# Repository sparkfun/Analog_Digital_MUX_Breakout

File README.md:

Analog/Digital MUX Breakout
===========================

[  
*Analog/Digital MUX Breakout (BOB-09056)*](https://www.sparkfun.com/products/9056)

This a breakout board for the 16-channel Analog/Digital Multiplexer/Demultiplier CD74HC4067. 

Repository Contents
-------------------
* **/Hardware** - All Eagle design files (.brd, .sch)

License Information
-------------------
The hardware is released under [Creative Commons Share-alike 3.0](http://creativecommons.org/licenses/by-sa/3.0/).

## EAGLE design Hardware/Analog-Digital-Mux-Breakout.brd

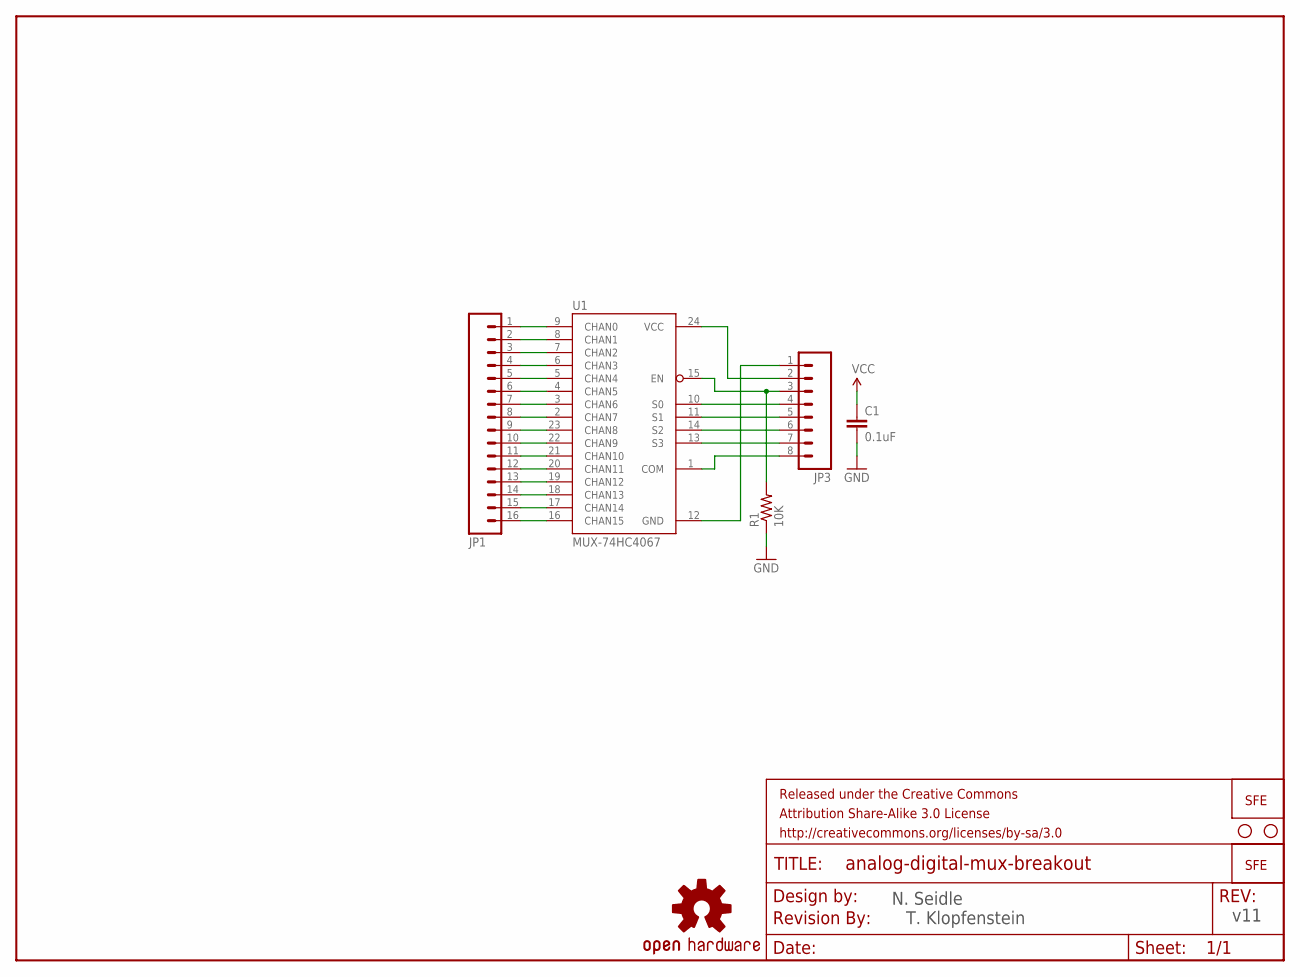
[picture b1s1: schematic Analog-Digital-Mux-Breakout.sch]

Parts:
C1: 0.1uF; 0603
FRAME1: FRAME-LETTER; CREATIVE_COMMONS
JP1: M16PTH; 1X16
JP3: M081X08; 1X08
LOGO1: OSHW-LOGOL; OSHW-LOGO-L
LOGO2: LOGO-SFESK; SFE-LOGO-FLAME
R1: 10K; 0603
STANDOFF1, STANDOFF2: STAND-OFF
U1: MUX-74HC4067; SSOP24
U$1: LOGO-SFENEW; SFE-NEW-WEBLOGO
U$2: REVISION

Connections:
C0: JP1.1, U1.9 (CHAN0)
C1: JP1.2, U1.8 (CHAN1)
C2: JP1.3, U1.7 (CHAN2)
C3: JP1.4, U1.6 (CHAN3)
C4: JP1.5, U1.5 (CHAN4)
C5: JP1.6, U1.4 (CHAN5)
C6: JP1.7, U1.3 (CHAN6)
C7: JP1.8, U1.2 (CHAN7)
C8: JP1.9, U1.23 (CHAN8)
C9: JP1.10, U1.22 (CHAN9)
C10: JP1.11, U1.21 (CHAN10)
C11: JP1.12, U1.20 (CHAN11)
C12: JP1.13, U1.19 (CHAN12)
C13: JP1.14, U1.18 (CHAN13)
C14: JP1.15, U1.17 (CHAN14)
C15: JP1.16, U1.16 (CHAN15)
EN: JP3.3, R1.2, U1.15 (EN)
GND: C1.2, JP3.1, R1.1, U1.12 (GND)
S0: JP3.4, U1.10 (S0)
S1: JP3.5, U1.11 (S1)
S2: JP3.6, U1.14 (S2)
S3: JP3.7, U1.13 (S3)
SIG: JP3.8, U1.1 (COM)
VCC: C1.1, JP3.2, U1.24 (VCC)

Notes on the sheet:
v11
N. Seidle
T. Klopfenstein

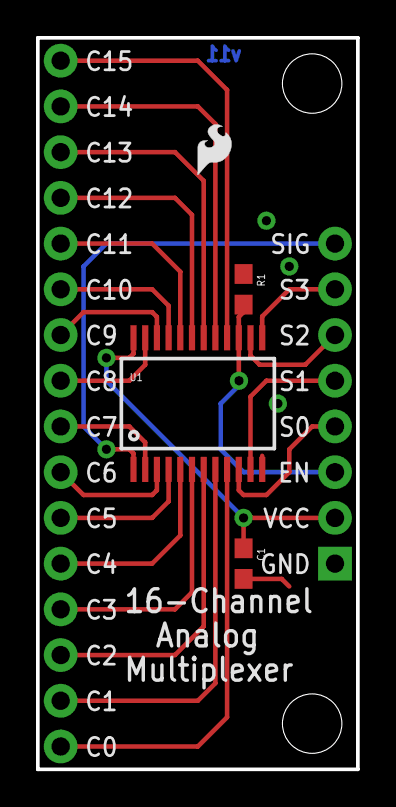
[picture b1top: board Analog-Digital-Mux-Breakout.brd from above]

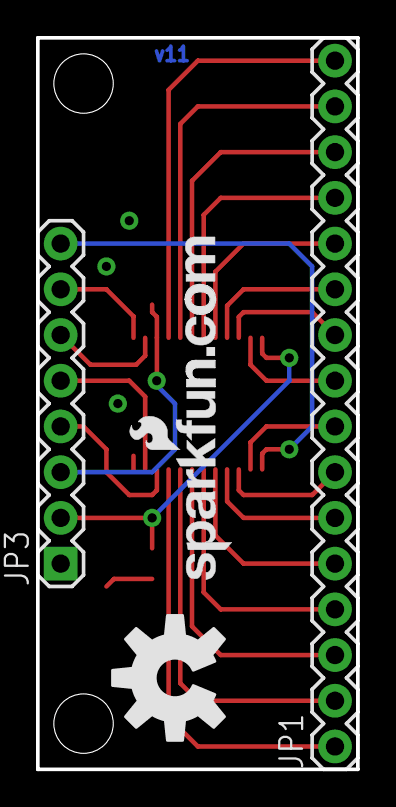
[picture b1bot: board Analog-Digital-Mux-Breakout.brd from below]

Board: 2 copper layers, 17.8 x 40.6 mm, 12 parts (4 on the bottom side), 24 nets.

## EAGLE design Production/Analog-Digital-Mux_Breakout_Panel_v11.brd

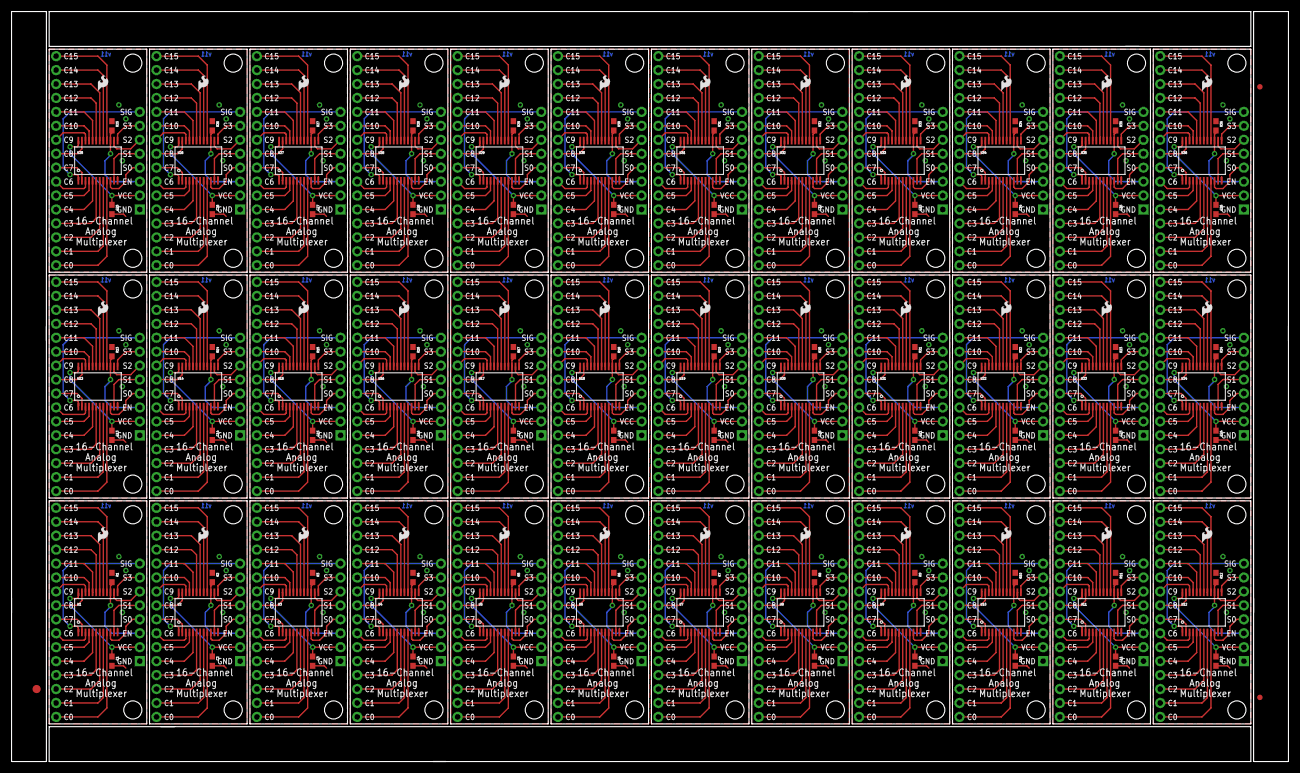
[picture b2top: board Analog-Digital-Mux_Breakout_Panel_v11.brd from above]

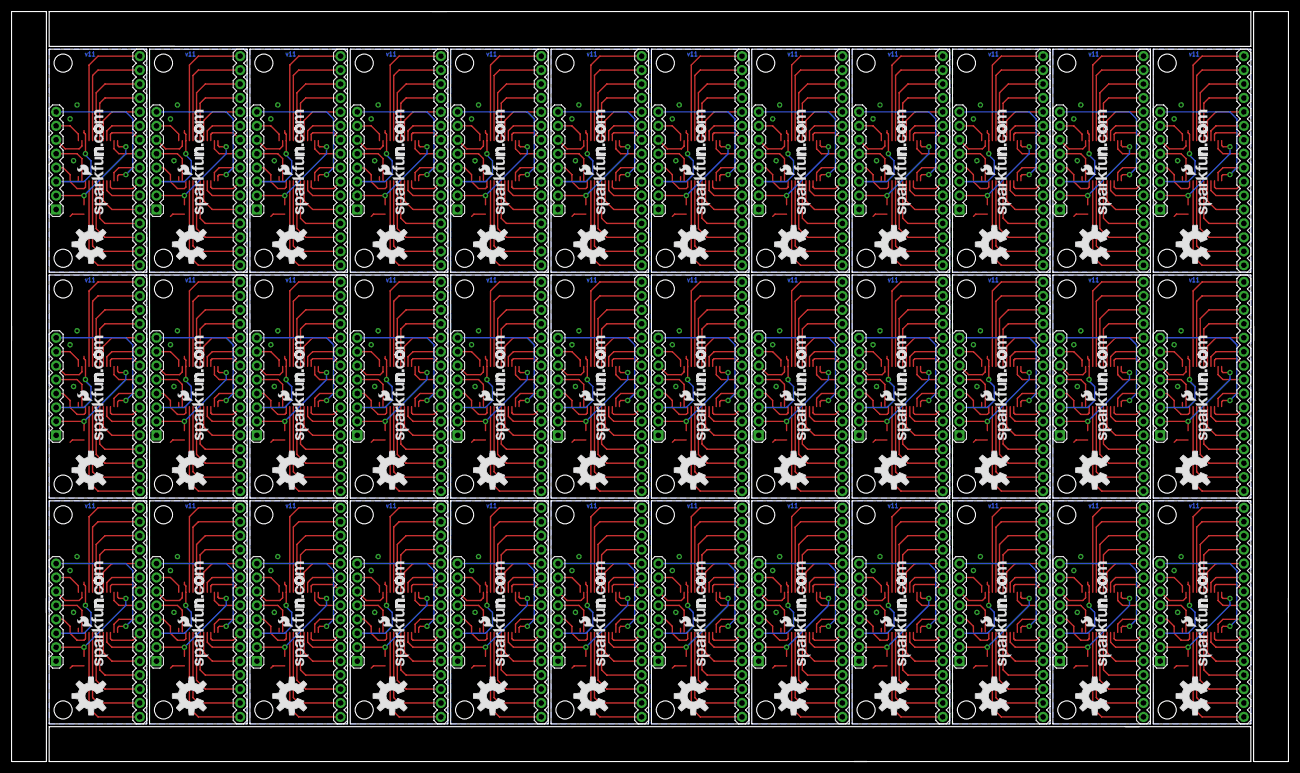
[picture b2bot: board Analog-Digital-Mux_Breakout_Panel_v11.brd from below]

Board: 2 copper layers, 232.7 x 136.7 mm, 363 parts (144 on the bottom side), 864 nets.

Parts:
C1, C2, C3, C4, C5, C6, C7, C8, C9, C10, C11, C12, C13, C14, C15, C16, C17, C18, C19, C20, C21, C22, C23, C24, C25, C26, C27, C28, C29, C30, C31, C32, C33, C34, C35, C36: 0.1uF; 0603
E$1: FIDUCIAL-1.5X3
E$5, E$6: FIDUCIAL-1X2
JP1, JP2, JP5, JP7, JP9, JP11, JP13, JP15, JP17, JP19, JP21, JP23, JP25, JP27, JP29, JP31, JP33, JP35, JP37, JP39, JP41, JP43, JP45, JP47, JP49, JP51, JP53, JP55, JP57, JP59, JP61, JP63, JP65, JP67, JP69, JP71: 1X16
JP3, JP4, JP6, JP8, JP10, JP12, JP14, JP16, JP18, JP20, JP22, JP24, JP26, JP28, JP30, JP32, JP34, JP36, JP38, JP40, JP42, JP44, JP46, JP48, JP50, JP52, JP54, JP56, JP58, JP60, JP62, JP64, JP66, JP68, JP70, JP72: 1X08
LOGO1, LOGO3, LOGO5, LOGO7, LOGO9, LOGO11, LOGO13, LOGO15, LOGO17, LOGO19, LOGO21, LOGO23, LOGO25, LOGO27, LOGO29, LOGO31, LOGO33, LOGO35, LOGO37, LOGO39, LOGO41, LOGO43, LOGO45, LOGO47, LOGO49, LOGO51, LOGO53, LOGO55, LOGO57, LOGO59, LOGO61, LOGO63, LOGO65, LOGO67, LOGO69, LOGO71: OSHW-LOGOL; OSHW-LOGO-L
LOGO2, LOGO4, LOGO6, LOGO8, LOGO10, LOGO12, LOGO14, LOGO16, LOGO18, LOGO20, LOGO22, LOGO24, LOGO26, LOGO28, LOGO30, LOGO32, LOGO34, LOGO36, LOGO38, LOGO40, LOGO42, LOGO44, LOGO46, LOGO48, LOGO50, LOGO52, LOGO54, LOGO56, LOGO58, LOGO60, LOGO62, LOGO64, LOGO66, LOGO68, LOGO70, LOGO72: LOGO-SFESK; SFE-LOGO-FLAME
R1, R2, R3, R4, R5, R6, R7, R8, R9, R10, R11, R12, R13, R14, R15, R16, R17, R18, R19, R20, R21, R22, R23, R24, R25, R26, R27, R28, R29, R30, R31, R32, R33, R34, R35, R36: 10K; 0603
STANDOFF1, STANDOFF2, STANDOFF3, STANDOFF4, STANDOFF5, STANDOFF6, STANDOFF7, STANDOFF8, STANDOFF9, STANDOFF10, STANDOFF11, STANDOFF12, STANDOFF13, STANDOFF14, STANDOFF15, STANDOFF16, STANDOFF17, STANDOFF18, STANDOFF19, STANDOFF20, STANDOFF21, STANDOFF22, STANDOFF23, STANDOFF24, STANDOFF25, STANDOFF26, STANDOFF27, STANDOFF28, STANDOFF29, STANDOFF30, STANDOFF31, STANDOFF32, STANDOFF33, STANDOFF34, STANDOFF35, STANDOFF36, STANDOFF37, STANDOFF38, STANDOFF39, STANDOFF40, STANDOFF41, STANDOFF42, STANDOFF43, STANDOFF44, STANDOFF45, STANDOFF46, STANDOFF47, STANDOFF48, STANDOFF49, STANDOFF50, STANDOFF51, STANDOFF52, STANDOFF53, STANDOFF54, STANDOFF55, STANDOFF56, STANDOFF57, STANDOFF58, STANDOFF59, STANDOFF60, STANDOFF61, STANDOFF62, STANDOFF63, STANDOFF64, STANDOFF65, STANDOFF66, STANDOFF67, STANDOFF68, STANDOFF69, STANDOFF70, STANDOFF71, STANDOFF72: STAND-OFF
U1, U2, U3, U4, U5, U6, U7, U8, U9, U10, U11, U12, U13, U14, U15, U16, U17, U18, U19, U20, U21, U22, U23, U24, U25, U26, U27, U28, U29, U30, U31, U32, U33, U34, U35, U36: MUX-74HC4067; SSOP24
U$1, U$2, U$3, U$4, U$5, U$6, U$7, U$8, U$9, U$10, U$11, U$12, U$13, U$14, U$15, U$16, U$17, U$18, U$19, U$20, U$21, U$22, U$23, U$24, U$25, U$26, U$27, U$28, U$29, U$30, U$31, U$32, U$33, U$34, U$35, U$36: LOGO-SFENEW; SFE-NEW-WEBLOGO

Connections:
C0: JP1.1, U1.9
C1: JP1.2, U1.8
C2: JP1.3, U1.7
C3: JP1.4, U1.6
C4: JP1.5, U1.5
C5: JP1.6, U1.4
C6: JP1.7, U1.3
C7: JP1.8, U1.2
C8: JP1.9, U1.23
C9: JP1.10, U1.22
C10: JP1.11, U1.21
C11: JP1.12, U1.20
C12: JP1.13, U1.19
C13: JP1.14, U1.18
C14: JP1.15, U1.17
C15: JP1.16, U1.16
C16: JP2.1, U2.9
C17: JP2.2, U2.8
C18: JP2.3, U2.7
C19: JP2.4, U2.6
C20: JP2.5, U2.5
C21: JP2.6, U2.4
C22: JP2.7, U2.3
C23: JP2.8, U2.2
C24: JP2.9, U2.23
C25: JP2.10, U2.22
C26: JP2.11, U2.21
C27: JP2.12, U2.20
C28: JP2.13, U2.19
C29: JP2.14, U2.18
C30: JP2.15, U2.17
C31: JP2.16, U2.16
C32: JP5.1, U3.9
C33: JP5.2, U3.8
C34: JP5.3, U3.7
C35: JP5.4, U3.6
C36: JP5.5, U3.5
C37: JP5.6, U3.4
C38: JP5.7, U3.3
C39: JP5.8, U3.2
C40: JP5.9, U3.23
C41: JP5.10, U3.22
C42: JP5.11, U3.21
C43: JP5.12, U3.20
C44: JP5.13, U3.19
C45: JP5.14, U3.18
C46: JP5.15, U3.17
C47: JP5.16, U3.16
C48: JP7.1, U4.9
C49: JP7.2, U4.8
C50: JP7.3, U4.7
C51: JP7.4, U4.6
C52: JP7.5, U4.5
C53: JP7.6, U4.4
C54: JP7.7, U4.3
C55: JP7.8, U4.2
C56: JP7.9, U4.23
C57: JP7.10, U4.22
C58: JP7.11, U4.21
C59: JP7.12, U4.20
C60: JP7.13, U4.19
C61: JP7.14, U4.18
C62: JP7.15, U4.17
C63: JP7.16, U4.16
C64: JP9.1, U5.9
C65: JP9.2, U5.8
C66: JP9.3, U5.7
C67: JP9.4, U5.6
C68: JP9.5, U5.5
C69: JP9.6, U5.4
C70: JP9.7, U5.3
C71: JP9.8, U5.2
C72: JP9.9, U5.23
C73: JP9.10, U5.22
C74: JP9.11, U5.21
C75: JP9.12, U5.20
C76: JP9.13, U5.19
C77: JP9.14, U5.18
C78: JP9.15, U5.17
C79: JP9.16, U5.16
C80: JP11.1, U6.9
C81: JP11.2, U6.8
C82: JP11.3, U6.7
C83: JP11.4, U6.6
C84: JP11.5, U6.5
C85: JP11.6, U6.4
C86: JP11.7, U6.3
C87: JP11.8, U6.2
C88: JP11.9, U6.23
C89: JP11.10, U6.22
C90: JP11.11, U6.21
C91: JP11.12, U6.20
C92: JP11.13, U6.19
C93: JP11.14, U6.18
C94: JP11.15, U6.17
C95: JP11.16, U6.16
C96: JP13.1, U7.9
C97: JP13.2, U7.8
C98: JP13.3, U7.7
C99: JP13.4, U7.6
C100: JP13.5, U7.5
C101: JP13.6, U7.4
C102: JP13.7, U7.3
C103: JP13.8, U7.2
C104: JP13.9, U7.23
C105: JP13.10, U7.22
C106: JP13.11, U7.21
C107: JP13.12, U7.20
C108: JP13.13, U7.19
C109: JP13.14, U7.18
C110: JP13.15, U7.17
C111: JP13.16, U7.16
C112: JP15.1, U8.9
C113: JP15.2, U8.8
C114: JP15.3, U8.7
C115: JP15.4, U8.6
C116: JP15.5, U8.5
C117: JP15.6, U8.4
C118: JP15.7, U8.3
C119: JP15.8, U8.2
C120: JP15.9, U8.23
C121: JP15.10, U8.22
C122: JP15.11, U8.21
C123: JP15.12, U8.20
C124: JP15.13, U8.19
C125: JP15.14, U8.18
C126: JP15.15, U8.17
C127: JP15.16, U8.16
C128: JP17.1, U9.9
C129: JP17.2, U9.8
C130: JP17.3, U9.7
C131: JP17.4, U9.6
C132: JP17.5, U9.5
C133: JP17.6, U9.4
C134: JP17.7, U9.3
C135: JP17.8, U9.2
C136: JP17.9, U9.23
C137: JP17.10, U9.22
C138: JP17.11, U9.21
C139: JP17.12, U9.20
C140: JP17.13, U9.19
C141: JP17.14, U9.18
C142: JP17.15, U9.17
C143: JP17.16, U9.16
C144: JP19.1, U10.9
C145: JP19.2, U10.8
C146: JP19.3, U10.7
C147: JP19.4, U10.6
C148: JP19.5, U10.5
C149: JP19.6, U10.4
C150: JP19.7, U10.3
C151: JP19.8, U10.2
C152: JP19.9, U10.23
C153: JP19.10, U10.22
C154: JP19.11, U10.21
C155: JP19.12, U10.20
C156: JP19.13, U10.19
C157: JP19.14, U10.18
C158: JP19.15, U10.17
C159: JP19.16, U10.16
C160: JP21.1, U11.9
C161: JP21.2, U11.8
C162: JP21.3, U11.7
C163: JP21.4, U11.6
C164: JP21.5, U11.5
C165: JP21.6, U11.4
C166: JP21.7, U11.3
C167: JP21.8, U11.2
C168: JP21.9, U11.23
C169: JP21.10, U11.22
C170: JP21.11, U11.21
C171: JP21.12, U11.20
C172: JP21.13, U11.19
C173: JP21.14, U11.18
C174: JP21.15, U11.17
C175: JP21.16, U11.16
C176: JP23.1, U12.9
C177: JP23.2, U12.8
C178: JP23.3, U12.7
C179: JP23.4, U12.6
C180: JP23.5, U12.5
C181: JP23.6, U12.4
C182: JP23.7, U12.3
C183: JP23.8, U12.2
C184: JP23.9, U12.23
C185: JP23.10, U12.22
C186: JP23.11, U12.21
C187: JP23.12, U12.20
C188: JP23.13, U12.19
C189: JP23.14, U12.18
C190: JP23.15, U12.17
C191: JP23.16, U12.16
C192: JP25.1, U13.9
C193: JP25.2, U13.8
C194: JP25.3, U13.7
C195: JP25.4, U13.6
C196: JP25.5, U13.5
C197: JP25.6, U13.4
C198: JP25.7, U13.3
C199: JP25.8, U13.2
C200: JP25.9, U13.23
C201: JP25.10, U13.22
C202: JP25.11, U13.21
C203: JP25.12, U13.20
C204: JP25.13, U13.19
C205: JP25.14, U13.18
C206: JP25.15, U13.17
C207: JP25.16, U13.16
C208: JP27.1, U14.9
C209: JP27.2, U14.8
C210: JP27.3, U14.7
C211: JP27.4, U14.6
C212: JP27.5, U14.5
C213: JP27.6, U14.4
C214: JP27.7, U14.3
C215: JP27.8, U14.2
C216: JP27.9, U14.23
C217: JP27.10, U14.22
C218: JP27.11, U14.21
C219: JP27.12, U14.20
C220: JP27.13, U14.19
C221: JP27.14, U14.18
C222: JP27.15, U14.17
C223: JP27.16, U14.16
C224: JP29.1, U15.9
C225: JP29.2, U15.8
C226: JP29.3, U15.7
C227: JP29.4, U15.6
C228: JP29.5, U15.5
C229: JP29.6, U15.4
C230: JP29.7, U15.3
C231: JP29.8, U15.2
C232: JP29.9, U15.23
C233: JP29.10, U15.22
C234: JP29.11, U15.21
C235: JP29.12, U15.20
C236: JP29.13, U15.19
C237: JP29.14, U15.18
C238: JP29.15, U15.17
C239: JP29.16, U15.16
C240: JP31.1, U16.9
C241: JP31.2, U16.8
C242: JP31.3, U16.7
C243: JP31.4, U16.6
C244: JP31.5, U16.5
C245: JP31.6, U16.4
C246: JP31.7, U16.3
C247: JP31.8, U16.2
C248: JP31.9, U16.23
C249: JP31.10, U16.22
C250: JP31.11, U16.21
C251: JP31.12, U16.20
C252: JP31.13, U16.19
C253: JP31.14, U16.18
C254: JP31.15, U16.17
C255: JP31.16, U16.16
C256: JP33.1, U17.9
C257: JP33.2, U17.8
C258: JP33.3, U17.7
C259: JP33.4, U17.6
C260: JP33.5, U17.5
C261: JP33.6, U17.4
C262: JP33.7, U17.3
C263: JP33.8, U17.2
C264: JP33.9, U17.23
C265: JP33.10, U17.22
C266: JP33.11, U17.21
C267: JP33.12, U17.20
C268: JP33.13, U17.19
C269: JP33.14, U17.18
C270: JP33.15, U17.17
C271: JP33.16, U17.16
C272: JP35.1, U18.9
C273: JP35.2, U18.8
C274: JP35.3, U18.7
C275: JP35.4, U18.6
C276: JP35.5, U18.5
C277: JP35.6, U18.4
C278: JP35.7, U18.3
C279: JP35.8, U18.2
C280: JP35.9, U18.23
C281: JP35.10, U18.22
C282: JP35.11, U18.21
C283: JP35.12, U18.20
C284: JP35.13, U18.19
C285: JP35.14, U18.18
C286: JP35.15, U18.17
C287: JP35.16, U18.16
C288: JP37.1, U19.9
C289: JP37.2, U19.8
C290: JP37.3, U19.7
C291: JP37.4, U19.6
C292: JP37.5, U19.5
C293: JP37.6, U19.4
C294: JP37.7, U19.3
C295: JP37.8, U19.2
C296: JP37.9, U19.23
C297: JP37.10, U19.22
C298: JP37.11, U19.21
C299: JP37.12, U19.20
C300: JP37.13, U19.19
C301: JP37.14, U19.18
C302: JP37.15, U19.17
C303: JP37.16, U19.16
C304: JP39.1, U20.9
C305: JP39.2, U20.8
C306: JP39.3, U20.7
C307: JP39.4, U20.6
C308: JP39.5, U20.5
C309: JP39.6, U20.4
C310: JP39.7, U20.3
C311: JP39.8, U20.2
C312: JP39.9, U20.23
C313: JP39.10, U20.22
C314: JP39.11, U20.21
C315: JP39.12, U20.20
C316: JP39.13, U20.19
C317: JP39.14, U20.18
C318: JP39.15, U20.17
C319: JP39.16, U20.16
C320: JP41.1, U21.9
C321: JP41.2, U21.8
C322: JP41.3, U21.7
C323: JP41.4, U21.6
C324: JP41.5, U21.5
C325: JP41.6, U21.4
C326: JP41.7, U21.3
C327: JP41.8, U21.2
C328: JP41.9, U21.23
C329: JP41.10, U21.22
C330: JP41.11, U21.21
C331: JP41.12, U21.20
C332: JP41.13, U21.19
C333: JP41.14, U21.18
C334: JP41.15, U21.17
C335: JP41.16, U21.16
C336: JP43.1, U22.9
C337: JP43.2, U22.8
C338: JP43.3, U22.7
C339: JP43.4, U22.6
C340: JP43.5, U22.5
C341: JP43.6, U22.4
C342: JP43.7, U22.3
C343: JP43.8, U22.2
C344: JP43.9, U22.23
C345: JP43.10, U22.22
C346: JP43.11, U22.21
C347: JP43.12, U22.20
C348: JP43.13, U22.19
C349: JP43.14, U22.18
C350: JP43.15, U22.17
C351: JP43.16, U22.16
C352: JP45.1, U23.9
C353: JP45.2, U23.8
C354: JP45.3, U23.7
C355: JP45.4, U23.6
C356: JP45.5, U23.5
C357: JP45.6, U23.4
C358: JP45.7, U23.3
C359: JP45.8, U23.2
C360: JP45.9, U23.23
C361: JP45.10, U23.22
C362: JP45.11, U23.21
C363: JP45.12, U23.20
C364: JP45.13, U23.19
C365: JP45.14, U23.18
C366: JP45.15, U23.17
C367: JP45.16, U23.16
C368: JP47.1, U24.9
C369: JP47.2, U24.8
C370: JP47.3, U24.7
C371: JP47.4, U24.6
C372: JP47.5, U24.5
C373: JP47.6, U24.4
C374: JP47.7, U24.3
C375: JP47.8, U24.2
C376: JP47.9, U24.23
C377: JP47.10, U24.22
C378: JP47.11, U24.21
C379: JP47.12, U24.20
C380: JP47.13, U24.19
C381: JP47.14, U24.18
C382: JP47.15, U24.17
C383: JP47.16, U24.16
C384: JP49.1, U25.9
C385: JP49.2, U25.8
C386: JP49.3, U25.7
C387: JP49.4, U25.6
C388: JP49.5, U25.5
C389: JP49.6, U25.4
C390: JP49.7, U25.3
C391: JP49.8, U25.2
C392: JP49.9, U25.23
C393: JP49.10, U25.22
C394: JP49.11, U25.21
C395: JP49.12, U25.20
C396: JP49.13, U25.19
C397: JP49.14, U25.18
C398: JP49.15, U25.17
C399: JP49.16, U25.16
C400: JP51.1, U26.9
C401: JP51.2, U26.8
C402: JP51.3, U26.7
C403: JP51.4, U26.6
C404: JP51.5, U26.5
C405: JP51.6, U26.4
C406: JP51.7, U26.3
C407: JP51.8, U26.2
C408: JP51.9, U26.23
C409: JP51.10, U26.22
C410: JP51.11, U26.21
C411: JP51.12, U26.20
C412: JP51.13, U26.19
C413: JP51.14, U26.18
C414: JP51.15, U26.17
C415: JP51.16, U26.16
C416: JP53.1, U27.9
C417: JP53.2, U27.8
C418: JP53.3, U27.7
C419: JP53.4, U27.6
C420: JP53.5, U27.5
C421: JP53.6, U27.4
C422: JP53.7, U27.3
C423: JP53.8, U27.2
C424: JP53.9, U27.23
C425: JP53.10, U27.22
C426: JP53.11, U27.21
C427: JP53.12, U27.20
C428: JP53.13, U27.19
C429: JP53.14, U27.18
C430: JP53.15, U27.17
C431: JP53.16, U27.16
C432: JP55.1, U28.9
C433: JP55.2, U28.8
C434: JP55.3, U28.7
C435: JP55.4, U28.6
C436: JP55.5, U28.5
C437: JP55.6, U28.4
C438: JP55.7, U28.3
C439: JP55.8, U28.2
C440: JP55.9, U28.23
C441: JP55.10, U28.22
C442: JP55.11, U28.21
C443: JP55.12, U28.20
C444: JP55.13, U28.19
C445: JP55.14, U28.18
C446: JP55.15, U28.17
C447: JP55.16, U28.16
C448: JP57.1, U29.9
C449: JP57.2, U29.8
C450: JP57.3, U29.7
C451: JP57.4, U29.6
C452: JP57.5, U29.5
C453: JP57.6, U29.4
C454: JP57.7, U29.3
C455: JP57.8, U29.2
C456: JP57.9, U29.23
C457: JP57.10, U29.22
C458: JP57.11, U29.21
C459: JP57.12, U29.20
C460: JP57.13, U29.19
C461: JP57.14, U29.18
C462: JP57.15, U29.17
C463: JP57.16, U29.16
C464: JP59.1, U30.9
C465: JP59.2, U30.8
C466: JP59.3, U30.7
C467: JP59.4, U30.6
C468: JP59.5, U30.5
C469: JP59.6, U30.4
C470: JP59.7, U30.3
C471: JP59.8, U30.2
C472: JP59.9, U30.23
C473: JP59.10, U30.22
C474: JP59.11, U30.21
C475: JP59.12, U30.20
C476: JP59.13, U30.19
C477: JP59.14, U30.18
C478: JP59.15, U30.17
C479: JP59.16, U30.16
C480: JP61.1, U31.9
C481: JP61.2, U31.8
C482: JP61.3, U31.7
C483: JP61.4, U31.6
C484: JP61.5, U31.5
C485: JP61.6, U31.4
C486: JP61.7, U31.3
C487: JP61.8, U31.2
C488: JP61.9, U31.23
C489: JP61.10, U31.22
C490: JP61.11, U31.21
C491: JP61.12, U31.20
C492: JP61.13, U31.19
C493: JP61.14, U31.18
C494: JP61.15, U31.17
C495: JP61.16, U31.16
C496: JP63.1, U32.9
C497: JP63.2, U32.8
C498: JP63.3, U32.7
C499: JP63.4, U32.6
C500: JP63.5, U32.5
C501: JP63.6, U32.4
C502: JP63.7, U32.3
C503: JP63.8, U32.2
C504: JP63.9, U32.23
C505: JP63.10, U32.22
C506: JP63.11, U32.21
C507: JP63.12, U32.20
C508: JP63.13, U32.19
C509: JP63.14, U32.18
C510: JP63.15, U32.17
C511: JP63.16, U32.16
C512: JP65.1, U33.9
C513: JP65.2, U33.8
C514: JP65.3, U33.7
C515: JP65.4, U33.6
C516: JP65.5, U33.5
C517: JP65.6, U33.4
C518: JP65.7, U33.3
C519: JP65.8, U33.2
C520: JP65.9, U33.23
C521: JP65.10, U33.22
C522: JP65.11, U33.21
C523: JP65.12, U33.20
C524: JP65.13, U33.19
C525: JP65.14, U33.18
C526: JP65.15, U33.17
C527: JP65.16, U33.16
C528: JP67.1, U34.9
C529: JP67.2, U34.8
C530: JP67.3, U34.7
C531: JP67.4, U34.6
C532: JP67.5, U34.5
C533: JP67.6, U34.4
C534: JP67.7, U34.3
C535: JP67.8, U34.2
C536: JP67.9, U34.23
C537: JP67.10, U34.22
C538: JP67.11, U34.21
C539: JP67.12, U34.20
C540: JP67.13, U34.19
C541: JP67.14, U34.18
C542: JP67.15, U34.17
C543: JP67.16, U34.16
C544: JP69.1, U35.9
C545: JP69.2, U35.8
C546: JP69.3, U35.7
C547: JP69.4, U35.6
C548: JP69.5, U35.5
C549: JP69.6, U35.4
C550: JP69.7, U35.3
C551: JP69.8, U35.2
C552: JP69.9, U35.23
C553: JP69.10, U35.22
C554: JP69.11, U35.21
C555: JP69.12, U35.20
C556: JP69.13, U35.19
C557: JP69.14, U35.18
C558: JP69.15, U35.17
C559: JP69.16, U35.16
C560: JP71.1, U36.9
C561: JP71.2, U36.8
C562: JP71.3, U36.7
C563: JP71.4, U36.6
C564: JP71.5, U36.5
C565: JP71.6, U36.4
C566: JP71.7, U36.3
C567: JP71.8, U36.2
C568: JP71.9, U36.23
C569: JP71.10, U36.22
C570: JP71.11, U36.21
C571: JP71.12, U36.20
C572: JP71.13, U36.19
C573: JP71.14, U36.18
C574: JP71.15, U36.17
C575: JP71.16, U36.16
EN: JP3.3, R1.2, U1.15
EN1: JP4.3, R2.2, U2.15
EN2: JP6.3, R3.2, U3.15
EN3: JP8.3, R4.2, U4.15
EN4: JP10.3, R5.2, U5.15
EN5: JP12.3, R6.2, U6.15
EN6: JP14.3, R7.2, U7.15
EN7: JP16.3, R8.2, U8.15
EN8: JP18.3, R9.2, U9.15
EN9: JP20.3, R10.2, U10.15
EN10: JP22.3, R11.2, U11.15
EN11: JP24.3, R12.2, U12.15
EN12: JP26.3, R13.2, U13.15
EN13: JP28.3, R14.2, U14.15
EN14: JP30.3, R15.2, U15.15
EN15: JP32.3, R16.2, U16.15
EN16: JP34.3, R17.2, U17.15
EN17: JP36.3, R18.2, U18.15
EN18: JP38.3, R19.2, U19.15
EN19: JP40.3, R20.2, U20.15
EN20: JP42.3, R21.2, U21.15
EN21: JP44.3, R22.2, U22.15
EN22: JP46.3, R23.2, U23.15
EN23: JP48.3, R24.2, U24.15
EN24: JP50.3, R25.2, U25.15
EN25: JP52.3, R26.2, U26.15
EN26: JP54.3, R27.2, U27.15
EN27: JP56.3, R28.2, U28.15
EN28: JP58.3, R29.2, U29.15
EN29: JP60.3, R30.2, U30.15
EN30: JP62.3, R31.2, U31.15
EN31: JP64.3, R32.2, U32.15
EN32: JP66.3, R33.2, U33.15
EN33: JP68.3, R34.2, U34.15
EN34: JP70.3, R35.2, U35.15
EN35: JP72.3, R36.2, U36.15
GND: C1.2, JP3.1, R1.1, U1.12
GND1: C2.2, JP4.1, R2.1, U2.12
GND2: C3.2, JP6.1, R3.1, U3.12
GND3: C4.2, JP8.1, R4.1, U4.12
GND4: C5.2, JP10.1, R5.1, U5.12
GND5: C6.2, JP12.1, R6.1, U6.12
GND6: C7.2, JP14.1, R7.1, U7.12
GND7: C8.2, JP16.1, R8.1, U8.12
GND8: C9.2, JP18.1, R9.1, U9.12
GND9: C10.2, JP20.1, R10.1, U10.12
GND10: C11.2, JP22.1, R11.1, U11.12
GND11: C12.2, JP24.1, R12.1, U12.12
GND12: C13.2, JP26.1, R13.1, U13.12
GND13: C14.2, JP28.1, R14.1, U14.12
GND14: C15.2, JP30.1, R15.1, U15.12
GND15: C16.2, JP32.1, R16.1, U16.12
GND16: C17.2, JP34.1, R17.1, U17.12
GND17: C18.2, JP36.1, R18.1, U18.12
GND18: C19.2, JP38.1, R19.1, U19.12
GND19: C20.2, JP40.1, R20.1, U20.12
GND20: C21.2, JP42.1, R21.1, U21.12
GND21: C22.2, JP44.1, R22.1, U22.12
GND22: C23.2, JP46.1, R23.1, U23.12
GND23: C24.2, JP48.1, R24.1, U24.12
GND24: C25.2, JP50.1, R25.1, U25.12
GND25: C26.2, JP52.1, R26.1, U26.12
GND26: C27.2, JP54.1, R27.1, U27.12
GND27: C28.2, JP56.1, R28.1, U28.12
GND28: C29.2, JP58.1, R29.1, U29.12
GND29: C30.2, JP60.1, R30.1, U30.12
GND30: C31.2, JP62.1, R31.1, U31.12
GND31: C32.2, JP64.1, R32.1, U32.12
GND32: C33.2, JP66.1, R33.1, U33.12
GND33: C34.2, JP68.1, R34.1, U34.12
GND34: C35.2, JP70.1, R35.1, U35.12
GND35: C36.2, JP72.1, R36.1, U36.12
S0: JP3.4, U1.10
S1: JP3.5, U1.11
S2: JP3.6, U1.14
S3: JP3.7, U1.13
S4: JP4.4, U2.10
S5: JP4.5, U2.11
S6: JP4.6, U2.14
S7: JP4.7, U2.13
S8: JP6.4, U3.10
S9: JP6.5, U3.11
S10: JP6.6, U3.14
S11: JP6.7, U3.13
S12: JP8.4, U4.10
S13: JP8.5, U4.11
S14: JP8.6, U4.14
S15: JP8.7, U4.13
S16: JP10.4, U5.10
S17: JP10.5, U5.11
S18: JP10.6, U5.14
S19: JP10.7, U5.13
S20: JP12.4, U6.10
S21: JP12.5, U6.11
S22: JP12.6, U6.14
S23: JP12.7, U6.13
S24: JP14.4, U7.10
S25: JP14.5, U7.11
S26: JP14.6, U7.14
S27: JP14.7, U7.13
S28: JP16.4, U8.10
S29: JP16.5, U8.11
S30: JP16.6, U8.14
S31: JP16.7, U8.13
S32: JP18.4, U9.10
S33: JP18.5, U9.11
S34: JP18.6, U9.14
S35: JP18.7, U9.13
S36: JP20.4, U10.10
S37: JP20.5, U10.11
S38: JP20.6, U10.14
S39: JP20.7, U10.13
S40: JP22.4, U11.10
S41: JP22.5, U11.11
S42: JP22.6, U11.14
S43: JP22.7, U11.13
S44: JP24.4, U12.10
S45: JP24.5, U12.11
S46: JP24.6, U12.14
S47: JP24.7, U12.13
S48: JP26.4, U13.10
S49: JP26.5, U13.11
S50: JP26.6, U13.14
S51: JP26.7, U13.13
S52: JP28.4, U14.10
S53: JP28.5, U14.11
S54: JP28.6, U14.14
S55: JP28.7, U14.13
S56: JP30.4, U15.10
S57: JP30.5, U15.11
S58: JP30.6, U15.14
S59: JP30.7, U15.13
S60: JP32.4, U16.10
S61: JP32.5, U16.11
S62: JP32.6, U16.14
S63: JP32.7, U16.13
S64: JP34.4, U17.10
S65: JP34.5, U17.11
S66: JP34.6, U17.14
S67: JP34.7, U17.13
S68: JP36.4, U18.10
S69: JP36.5, U18.11
S70: JP36.6, U18.14
S71: JP36.7, U18.13
S72: JP38.4, U19.10
S73: JP38.5, U19.11
S74: JP38.6, U19.14
S75: JP38.7, U19.13
S76: JP40.4, U20.10
S77: JP40.5, U20.11
S78: JP40.6, U20.14
S79: JP40.7, U20.13
S80: JP42.4, U21.10
S81: JP42.5, U21.11
S82: JP42.6, U21.14
S83: JP42.7, U21.13
S84: JP44.4, U22.10
S85: JP44.5, U22.11
S86: JP44.6, U22.14
S87: JP44.7, U22.13
S88: JP46.4, U23.10
S89: JP46.5, U23.11
S90: JP46.6, U23.14
S91: JP46.7, U23.13
S92: JP48.4, U24.10
S93: JP48.5, U24.11
S94: JP48.6, U24.14
S95: JP48.7, U24.13
S96: JP50.4, U25.10
S97: JP50.5, U25.11
S98: JP50.6, U25.14
S99: JP50.7, U25.13
S100: JP52.4, U26.10
S101: JP52.5, U26.11
S102: JP52.6, U26.14
S103: JP52.7, U26.13
S104: JP54.4, U27.10
S105: JP54.5, U27.11
S106: JP54.6, U27.14
S107: JP54.7, U27.13
S108: JP56.4, U28.10
S109: JP56.5, U28.11
S110: JP56.6, U28.14
S111: JP56.7, U28.13
S112: JP58.4, U29.10
S113: JP58.5, U29.11
S114: JP58.6, U29.14
S115: JP58.7, U29.13
S116: JP60.4, U30.10
S117: JP60.5, U30.11
S118: JP60.6, U30.14
S119: JP60.7, U30.13
S120: JP62.4, U31.10
S121: JP62.5, U31.11
S122: JP62.6, U31.14
S123: JP62.7, U31.13
S124: JP64.4, U32.10
S125: JP64.5, U32.11
S126: JP64.6, U32.14
S127: JP64.7, U32.13
S128: JP66.4, U33.10
S129: JP66.5, U33.11
S130: JP66.6, U33.14
S131: JP66.7, U33.13
S132: JP68.4, U34.10
S133: JP68.5, U34.11
S134: JP68.6, U34.14
S135: JP68.7, U34.13
S136: JP70.4, U35.10
S137: JP70.5, U35.11
S138: JP70.6, U35.14
S139: JP70.7, U35.13
S140: JP72.4, U36.10
S141: JP72.5, U36.11
S142: JP72.6, U36.14
S143: JP72.7, U36.13
SIG: JP3.8, U1.1
SIG1: JP4.8, U2.1
SIG2: JP6.8, U3.1
SIG3: JP8.8, U4.1
SIG4: JP10.8, U5.1
SIG5: JP12.8, U6.1
SIG6: JP14.8, U7.1
SIG7: JP16.8, U8.1
SIG8: JP18.8, U9.1
SIG9: JP20.8, U10.1
SIG10: JP22.8, U11.1
SIG11: JP24.8, U12.1
SIG12: JP26.8, U13.1
SIG13: JP28.8, U14.1
SIG14: JP30.8, U15.1
SIG15: JP32.8, U16.1
SIG16: JP34.8, U17.1
SIG17: JP36.8, U18.1
SIG18: JP38.8, U19.1
SIG19: JP40.8, U20.1
SIG20: JP42.8, U21.1
SIG21: JP44.8, U22.1
SIG22: JP46.8, U23.1
SIG23: JP48.8, U24.1
SIG24: JP50.8, U25.1
SIG25: JP52.8, U26.1
SIG26: JP54.8, U27.1
SIG27: JP56.8, U28.1
SIG28: JP58.8, U29.1
SIG29: JP60.8, U30.1
SIG30: JP62.8, U31.1
SIG31: JP64.8, U32.1
SIG32: JP66.8, U33.1
SIG33: JP68.8, U34.1
SIG34: JP70.8, U35.1
SIG35: JP72.8, U36.1
VCC: C1.1, JP3.2, U1.24
VCC1: C2.1, JP4.2, U2.24
VCC2: C3.1, JP6.2, U3.24
VCC3: C4.1, JP8.2, U4.24
VCC4: C5.1, JP10.2, U5.24
VCC5: C6.1, JP12.2, U6.24
VCC6: C7.1, JP14.2, U7.24
VCC7: C8.1, JP16.2, U8.24
VCC8: C9.1, JP18.2, U9.24
VCC9: C10.1, JP20.2, U10.24
VCC10: C11.1, JP22.2, U11.24
VCC11: C12.1, JP24.2, U12.24
VCC12: C13.1, JP26.2, U13.24
VCC13: C14.1, JP28.2, U14.24
VCC14: C15.1, JP30.2, U15.24
VCC15: C16.1, JP32.2, U16.24
VCC16: C17.1, JP34.2, U17.24
VCC17: C18.1, JP36.2, U18.24
VCC18: C19.1, JP38.2, U19.24
VCC19: C20.1, JP40.2, U20.24
VCC20: C21.1, JP42.2, U21.24
VCC21: C22.1, JP44.2, U22.24
VCC22: C23.1, JP46.2, U23.24
VCC23: C24.1, JP48.2, U24.24
VCC24: C25.1, JP50.2, U25.24
VCC25: C26.1, JP52.2, U26.24
VCC26: C27.1, JP54.2, U27.24
VCC27: C28.1, JP56.2, U28.24
VCC28: C29.1, JP58.2, U29.24
VCC29: C30.1, JP60.2, U30.24
VCC30: C31.1, JP62.2, U31.24
VCC31: C32.1, JP64.2, U32.24
VCC32: C33.1, JP66.2, U33.24
VCC33: C34.1, JP68.2, U34.24
VCC34: C35.1, JP70.2, U35.24
VCC35: C36.1, JP72.2, U36.24

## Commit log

2013-07-09 Updated hardware files with OSHW/larger annular rings
2013-07-15 Updated Revision to symbol
2013-07-17 v11 production ready
    created panel of 18
2015-09-15 :lollipop: Added .gitattributes & .gitignore files
2015-09-15 Initial Commit
    First Iteration of the the 16-Channel Analog Multiplexer/Demultiplexer
    CD74HC4067 Class.
2015-09-15 Implemented MUX CD74HC4067 by utilizing Multidimensional Arrays. This resulted in exceptions when deploying to Netduino. The .NET Micro Framework does not implement Multidimensional Arrays.
2015-09-15 Third Iteration
    The .NET Micro Framework doesn't implement Multidimensional Arrays,
    however, it does implement Jagged Arrays...
2015-10-16 new v11 panel
2015-12-07 Subtree merged in NETMF
    Merged NetduinoMUX repo into NETMF directory. NetduinoMUX is a project
    adapted from Analog_Digital_MUX_Breakout repo so that the CD74HC4067
    Class can be utilized with the .Net Micro Framework for the Netduino.
2018-04-18 Adding dimensions
2025-06-27 Update README.md
    Updating link

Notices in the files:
parts and their libraries:
SparkFun-Aesthetics: Licensing: CC v3.0 Share-Alike You are welcome to use this library for commercial purposes.
SparkFun-Aesthetics: Released under the Creative Commons Attribution Share-Alike 3.0 License
SparkFun-Aesthetics: Released under the Creative Commons
